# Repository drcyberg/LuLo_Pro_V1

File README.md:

### Content moved: [Link](https://github.com/drcyberg/MoonWalker_V1 "Link")

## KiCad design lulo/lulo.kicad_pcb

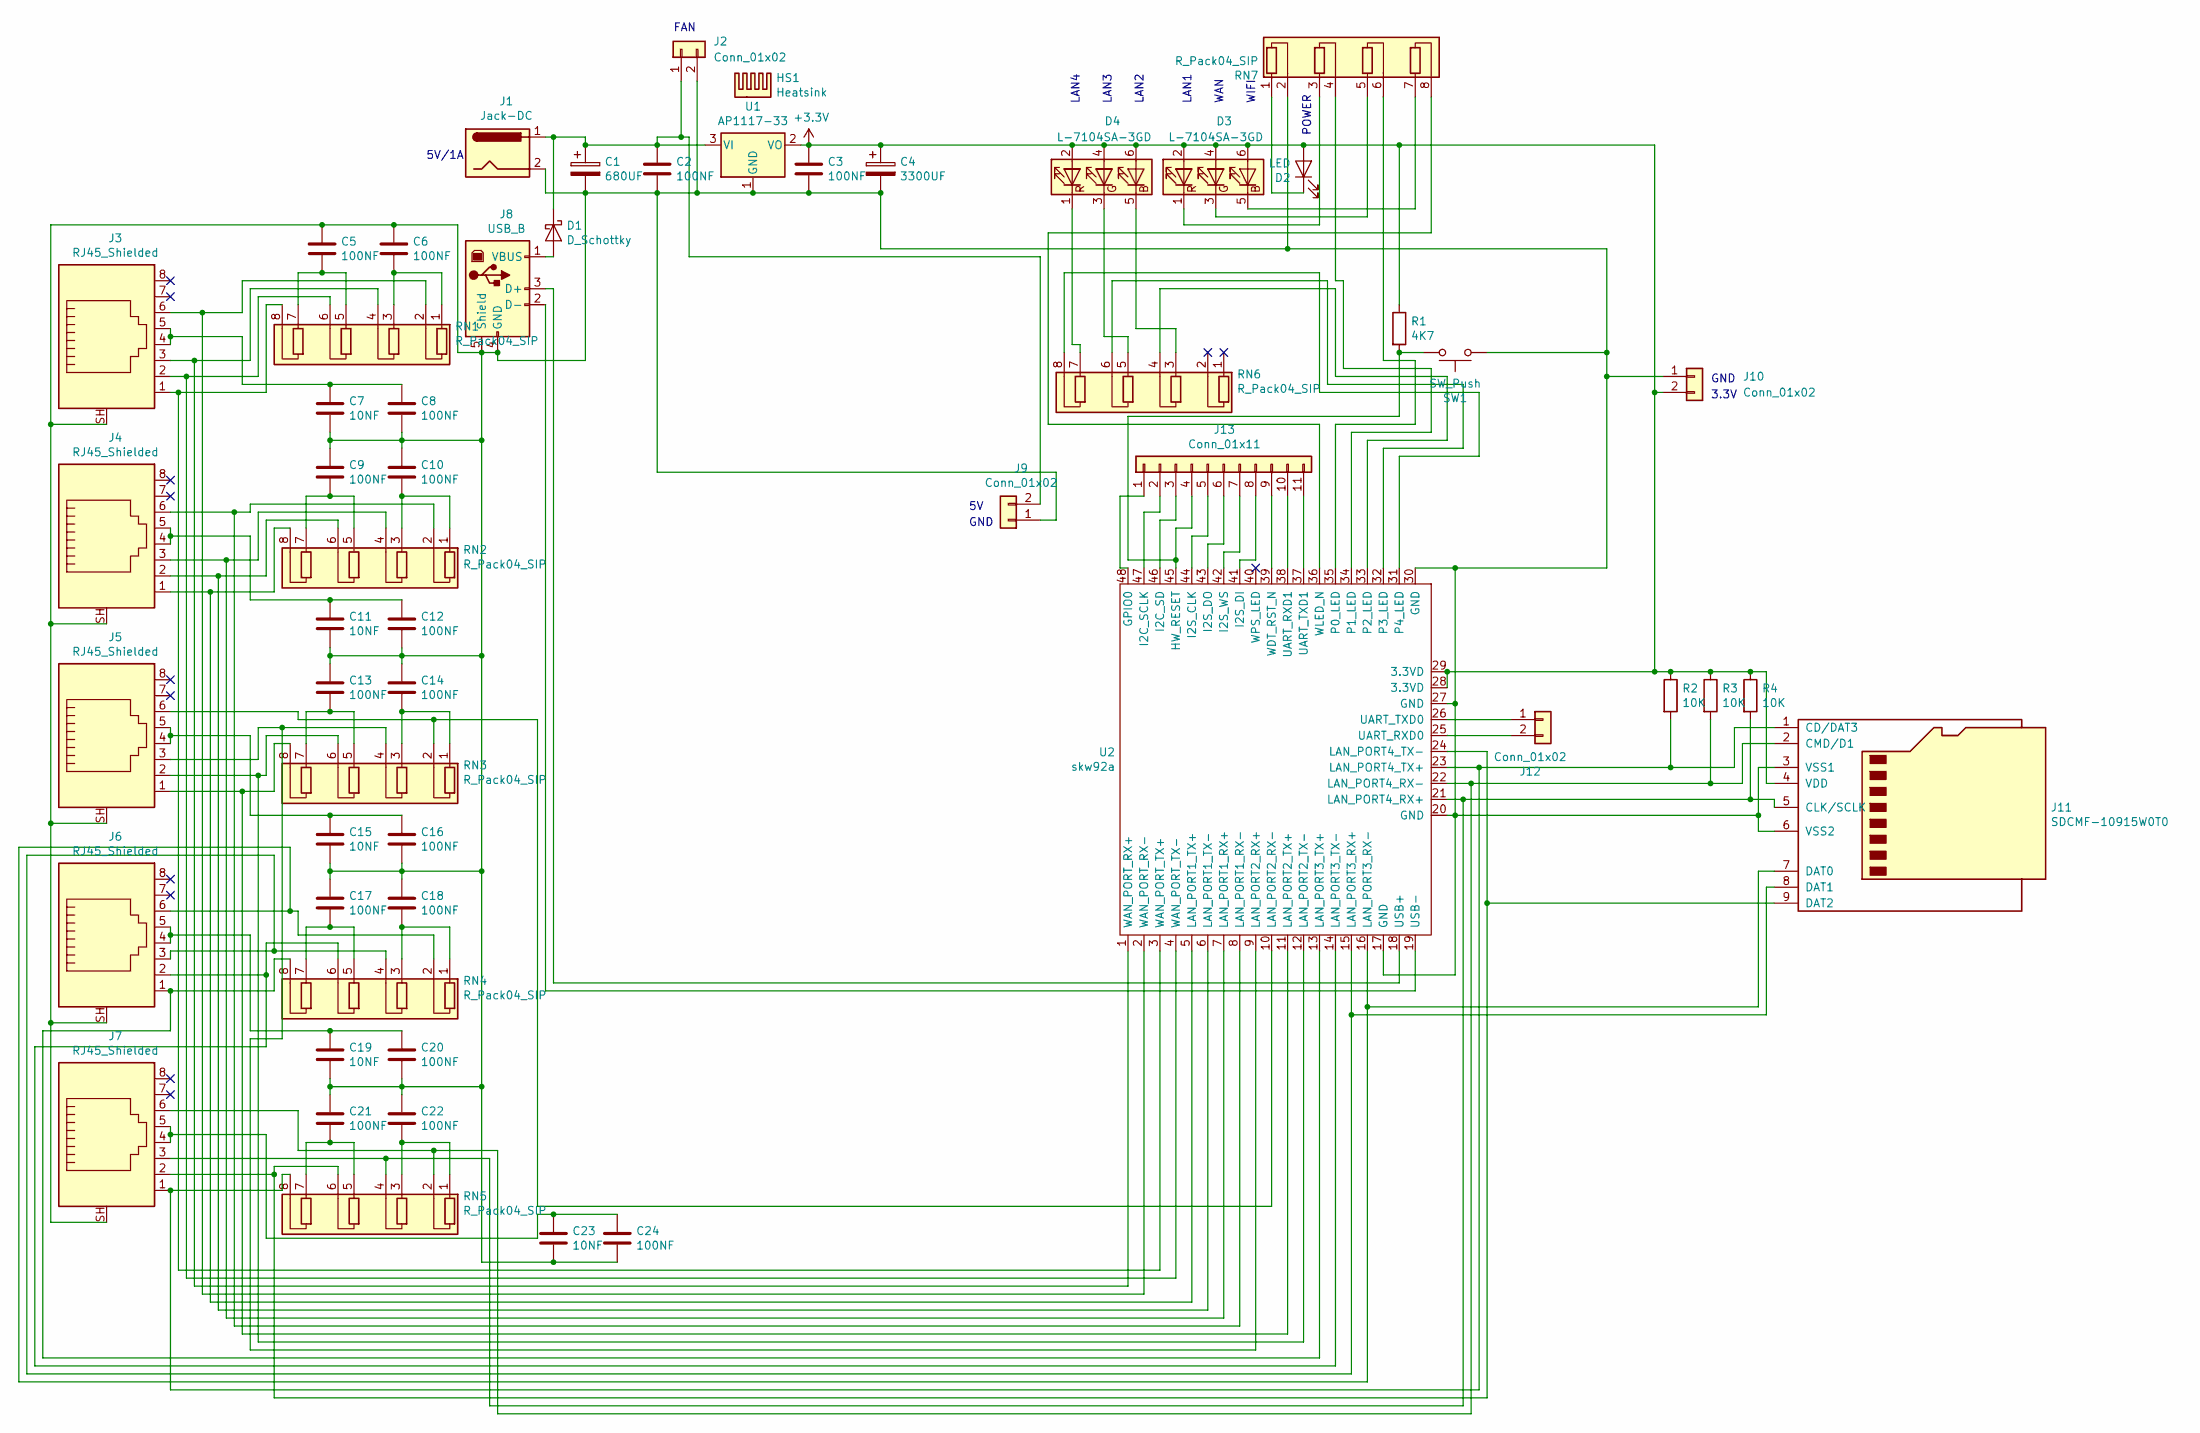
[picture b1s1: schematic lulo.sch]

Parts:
C1: 680UF; CP_Radial_D8.0mm_P3.50mm
C2, C3, C5, C6, C8, C9, C10, C12, C13, C14, C16, C17, C18, C20, C21, C22, C24: 100NF; C_Disc_D3.0mm_W1.6mm_P2.50mm
C4: 3300UF; CP_Radial_D12.5mm_P5.00mm
C7, C11, C15, C19, C23: 10NF; C_Disc_D3.0mm_W1.6mm_P2.50mm
D1: D_Schottky; D_DO-41_SOD81_P10.16mm_Horizontal
D2: LED; LED_D3.0mm
D3, D4: L-7104SA-3GD
HS1: Heatsink; D01A_Heat_Sink
J1: Jack-DC; BarrelJack_Horizontal
J2: Conn_01x02; kk100_22-23-2021
J3, J4, J5, J6, J7: RJ45_Shielded; SI-60008-F
J8: USB_B; USB_B_OST_USB-B1HSxx_Horizontal
J9, J10, J12: Conn_01x02; PinHeader_1x02_P2.54mm_Vertical
J11: SDCMF-10915W0T0; SD_TE_2041021
J13: Conn_01x11; PinHeader_1x11_P2.54mm_Vertical
R1: 4K7; R_Axial_DIN0207_L6.3mm_D2.5mm_P10.16mm_Horizontal
R2, R3, R4: 10K; R_Axial_DIN0207_L6.3mm_D2.5mm_P10.16mm_Horizontal
RN1, RN2, RN3, RN4, RN5, RN6, RN7: R_Pack04_SIP; R_Array_SIP8
SW1: SW_Push; SW_Tactile_SKHH_Angled
U1: AP1117-33; TO-220-3_Horizontal_TabDown
U2: skw92a; SKW92A

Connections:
+3V3: C3.1, C4.1, D2.2 (A), D3.2 (RA), D3.4 (GA), D3.6 (BA), D4.2 (RA), D4.4 (GA), D4.6 (BA), J10.2, J11.4 (VDD), R1.1, R2.1, R3.1, R4.1, U1.2 (VO), U2.28 (3.3VD), U2.29 (3.3VD)
unnamed: C1.1, C2.1, D1.1 (K), J1.1, J2.1, J9.2, U1.3 (VI)
unnamed: C1.2, C2.2, C3.2, C4.2, C5.1, C6.1, C7.2, C8.2, C9.1, C10.1, C11.2, C12.2, C13.1, C14.1, C15.2, C16.2, C17.1, C18.1, C19.2, C20.2, C21.1, C22.1, C23.2, C24.2, J1.2, J2.2, J3.SH, J4.SH, J5.SH, J6.SH, J7.SH, J8.4 (GND), J8.5 (Shield), J9.1, J10.1, J11.3 (VSS1), J11.6 (VSS2), RN7.2 (R1.2), SW1.1, U1.1 (GND), U2.17 (GND), U2.20 (GND), U2.27 (GND), U2.30 (GND)
unnamed: C5.2, RN1.5 (R3.1), RN1.7 (R4.1)
unnamed: C6.2, RN1.1 (R1.1), RN1.3 (R2.1)
unnamed: C7.1, C8.1, J3.4, J3.5
unnamed: C9.2, RN2.5 (R3.1), RN2.7 (R4.1)
unnamed: C10.2, RN2.1 (R1.1), RN2.3 (R2.1)
unnamed: C11.1, C12.1, J4.4, J4.5
unnamed: C13.2, RN3.5 (R3.1), RN3.7 (R4.1)
unnamed: C14.2, RN3.1 (R1.1), RN3.3 (R2.1)
unnamed: C15.1, C16.1, J5.4, J5.5
unnamed: C17.2, RN4.5 (R3.1), RN4.7 (R4.1)
unnamed: C18.2, RN4.1 (R1.1), RN4.3 (R2.1)
unnamed: C19.1, C20.1, J6.4, J6.5
unnamed: C21.2, RN5.5 (R3.1), RN5.7 (R4.1)
unnamed: C22.2, RN5.1 (R1.1), RN5.3 (R2.1)
unnamed: C23.1, C24.1, J7.4, J7.5
unnamed: D1.2 (A), J8.1 (VBUS)
unnamed: D2.1 (K), RN7.1 (R1.1)
unnamed: D3.1 (RK), RN7.3 (R2.1)
unnamed: D3.3 (GK), RN7.5 (R3.1)
unnamed: D3.5 (BK), RN7.7 (R4.1)
unnamed: D4.1 (RK), RN6.7 (R4.1)
unnamed: D4.3 (GK), RN6.5 (R3.1)
unnamed: D4.5 (BK), RN6.3 (R2.1)
unnamed: J3.1, RN1.8 (R4.2), U2.3 (WAN_PORT_TX+)
unnamed: J3.2, RN1.6 (R3.2), U2.4 (WAN_PORT_TX-)
unnamed: J3.3, RN1.4 (R2.2), U2.1 (WAN_PORT_RX+)
unnamed: J3.6, RN1.2 (R1.2), U2.2 (WAN_PORT_RX-)
unnamed: J4.1, RN2.8 (R4.2), U2.5 (LAN_PORT1_TX+)
unnamed: J4.2, RN2.6 (R3.2), U2.6 (LAN_PORT1_TX-)
unnamed: J4.3, RN2.4 (R2.2), U2.7 (LAN_PORT1_RX+)
unnamed: J4.6, RN2.2 (R1.2), U2.8 (LAN_PORT1_RX-)
unnamed: J5.1, RN3.8 (R4.2), U2.11 (LAN_PORT2_TX+)
unnamed: J5.2, RN3.6 (R3.2), U2.12 (LAN_PORT2_TX-)
unnamed: J5.3, RN3.4 (R2.2), U2.9 (LAN_PORT2_RX+)
unnamed: J5.6, RN3.2 (R1.2), U2.10 (LAN_PORT2_RX-)
unnamed: J6.1, RN4.8 (R4.2), U2.13 (LAN_PORT3_TX+)
unnamed: J6.2, RN4.6 (R3.2), U2.14 (LAN_PORT3_TX-)
unnamed: J8.2 (D-), U2.19 (USB-)
unnamed: J8.3 (D+), U2.18 (USB+)
unnamed: J7.1, J11.1 (CD/DAT3), R2.2, RN5.8 (R4.2), U2.23 (LAN_PORT4_TX+)
unnamed: J7.6, J11.2 (CMD/D1), R3.2, RN5.2 (R1.2), U2.22 (LAN_PORT4_RX-)
unnamed: J7.3, J11.5 (CLK/SCLK), R4.2, RN5.4 (R2.2), U2.21 (LAN_PORT4_RX+)
unnamed: J6.6, J11.7 (DAT0), RN4.2 (R1.2), U2.16 (LAN_PORT3_RX-)
unnamed: J6.3, J11.8 (DAT1), RN4.4 (R2.2), U2.15 (LAN_PORT3_RX+)
unnamed: J7.2, J11.9 (DAT2), RN5.6 (R3.2), U2.24 (LAN_PORT4_TX-)
unnamed: J12.1, U2.26 (UART_TXD0)
unnamed: J12.2, U2.25 (UART_RXD0)
unnamed: J13.1, U2.48 (GPIO0)
unnamed: J13.2, U2.47 (I2C_SCLK)
unnamed: J13.3, U2.46 (I2C_SD)
unnamed: J13.4, R1.2, SW1.2, U2.45 (HW_RESET)
unnamed: J13.5, U2.44 (I2S_CLK)
unnamed: J13.6, U2.43 (I2S_DO)
unnamed: J13.7, U2.42 (I2S_WS)
unnamed: J13.8, U2.41 (I2S_DI)
unnamed: J13.9, U2.39 (WDT_RST_N)
unnamed: J13.10, U2.38 (UART_RXD1)
unnamed: J13.11, U2.37 (UART_TXD1)
unnamed: RN6.4 (R2.2), U2.33 (P2_LED)
unnamed: RN6.6 (R3.2), U2.32 (P3_LED)
unnamed: RN6.8 (R4.2), U2.31 (P4_LED)
unnamed: RN7.4 (R2.2), U2.34 (P1_LED)
unnamed: RN7.6 (R3.2), U2.35 (P0_LED)
unnamed: RN7.8 (R4.2), U2.36 (WLED_N)

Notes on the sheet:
WAN
LAN1
LAN2
LAN3
LAN4
GND
FAN
3.3V
WIFI
POWER
5V/1A

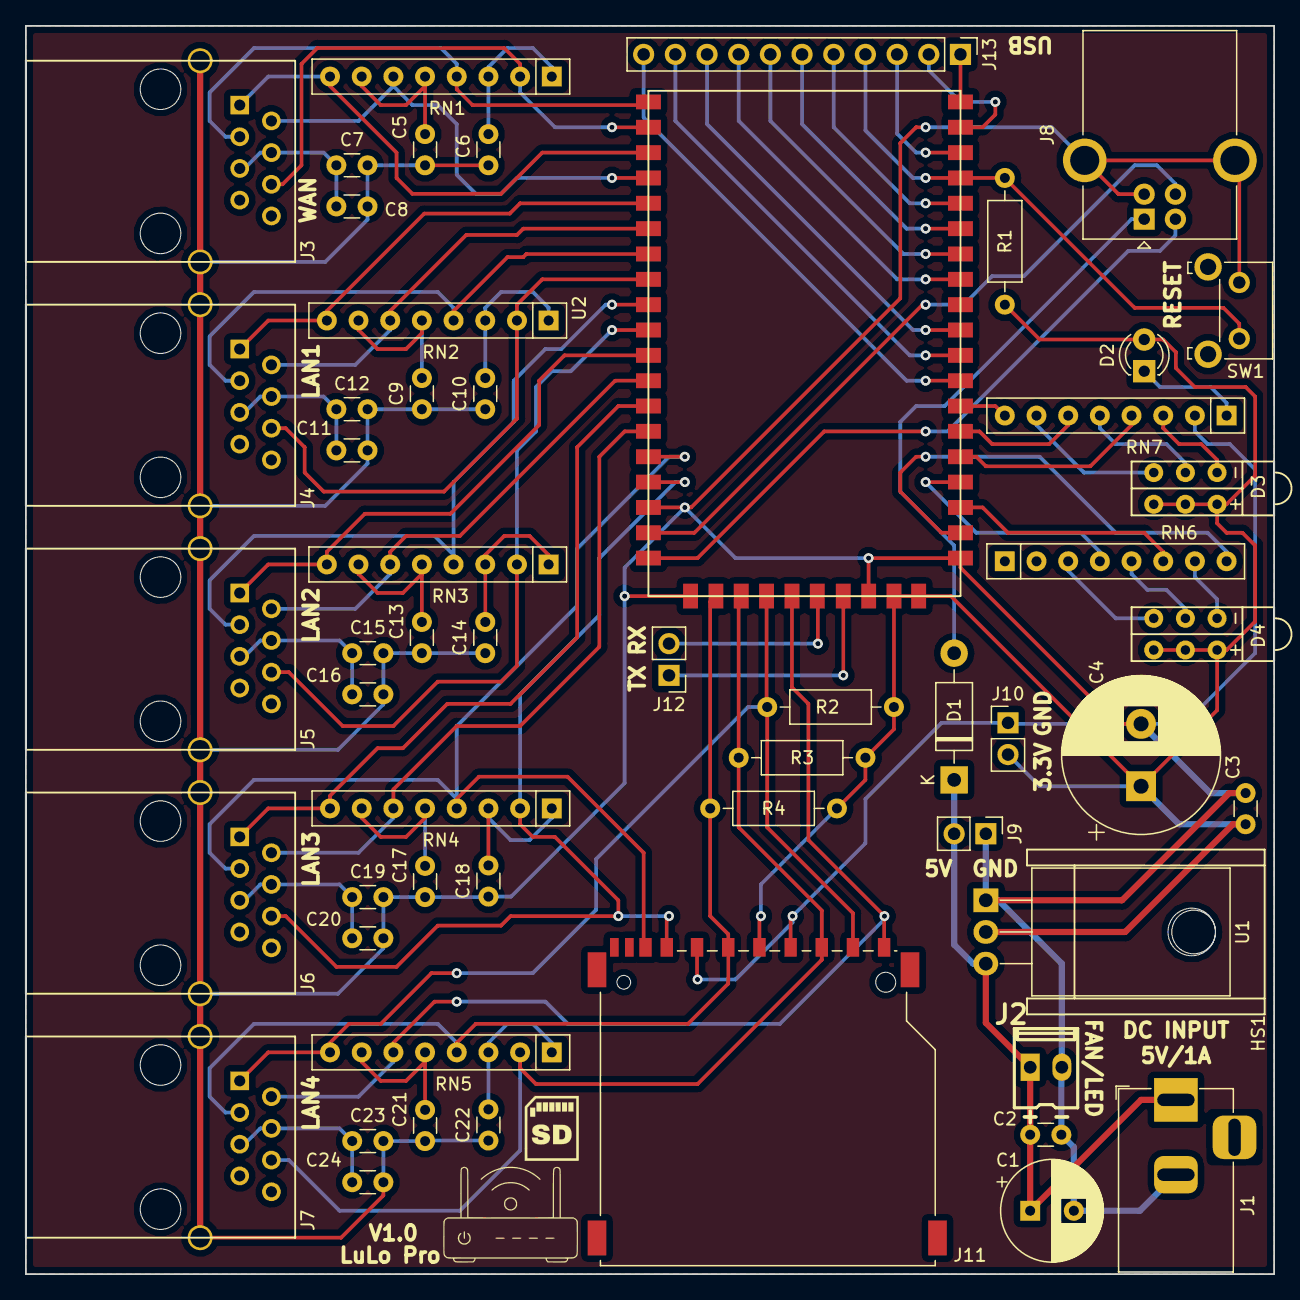
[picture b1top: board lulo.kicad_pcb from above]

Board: 2 copper layers, 100.1 x 100.1 mm, 56 parts (0 on the bottom side), 67 nets.

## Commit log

2020-09-24 Set theme jekyll-theme-tactile
2020-09-24 Set theme jekyll-theme-architect
2020-09-24 Set theme jekyll-theme-time-machine
2020-09-24 Set theme jekyll-theme-cayman
2020-09-25 Create valami
2020-09-27 Update from Forestry.io - Updated Forestry configuration
2020-09-27 (Grav GitSync) Automatic Commit from drcyberg@tutanota.com
2020-09-27 Set theme jekyll-theme-slate
2020-09-27 Set theme jekyll-theme-merlot
2020-09-27 Set theme jekyll-theme-minimal
